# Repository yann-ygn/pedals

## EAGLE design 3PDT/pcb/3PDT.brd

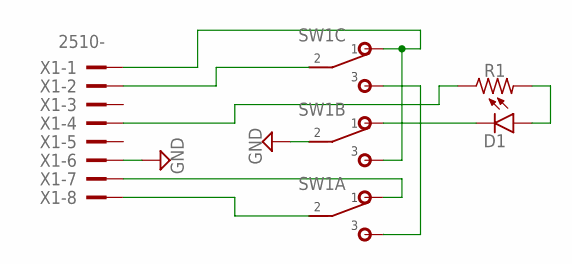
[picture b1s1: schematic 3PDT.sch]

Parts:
D1: LED; 3MM_D
R1: R_.3B; R0207/3
SW1: 3PDT
X1: 2510-; PAK100/2500-10

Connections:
GND: SW1.B2 (2), X1.6
unnamed: SW1.A3 (3), SW1.C3 (3)
unnamed: SW1.C2 (2), X1.2
unnamed: SW1.B3 (3), SW1.C1 (1), X1.1
unnamed: SW1.A2 (2), X1.8
unnamed: SW1.A1 (1), X1.7
unnamed: R1.1, X1.4
unnamed: D1.ANODE (A), R1.2
unnamed: D1.P$1 (C), SW1.B1 (1)

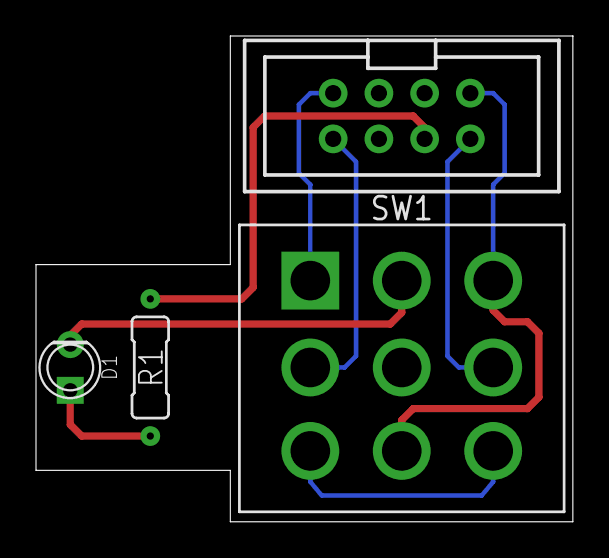
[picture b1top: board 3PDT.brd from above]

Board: 2 copper layers, 29.8 x 27.0 mm, 4 parts (0 on the bottom side), 9 nets.

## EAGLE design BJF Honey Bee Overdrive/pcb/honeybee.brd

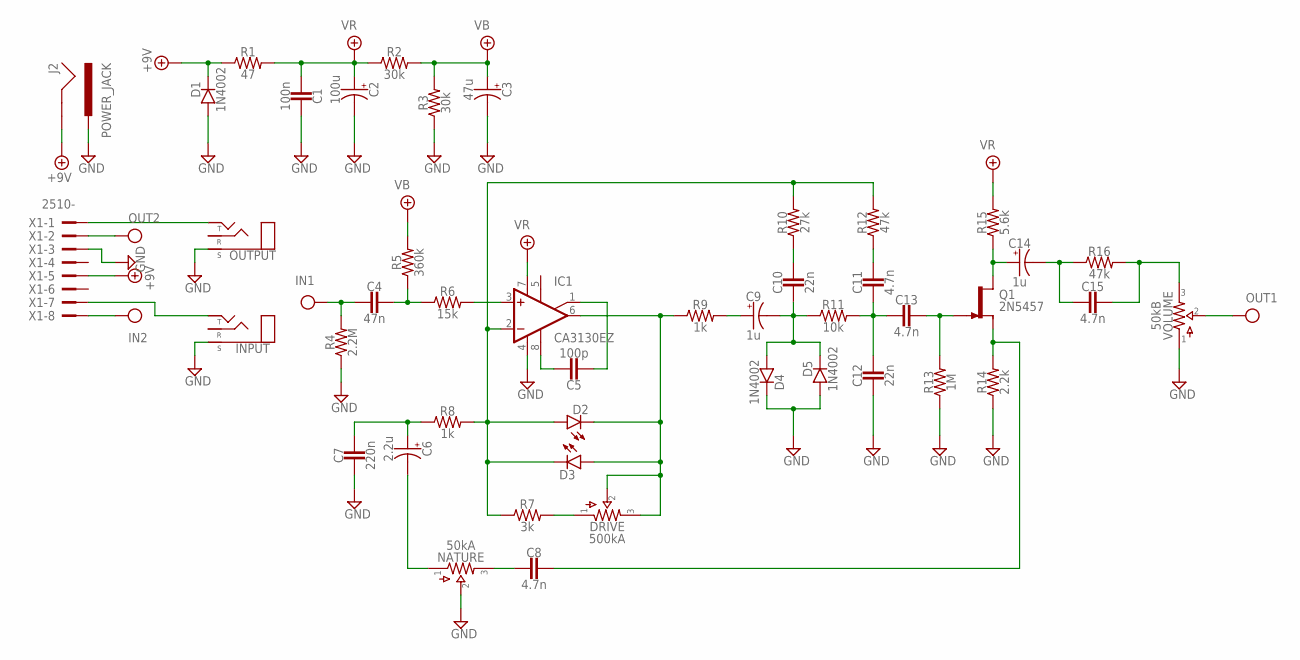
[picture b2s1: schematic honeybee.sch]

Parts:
C1: 100n; 050X030_025_2
C2: 100u; 040_020
C3: 47u; 040_020
C4: 47n; BOX_SMALL
C5: 100p; 050X030_025_2
C6: 2.2u; 050_020
C7: 220n; BOX_SMALL
C8, C11, C13, C15: 4.7n; BOX_SMALL
C9, C14: 1u; 040_020
C10, C12: 22n; BOX_SMALL
D1, D4, D5: 1N4002; DO41-2
D2, D3: LED; 3MM_D
DRIVE: 500kA; 16MM
IC1: CA3130EZ; DIL08
INPUT: STEREONMJ; NMJ6HCD2
J2: POWER_JACK; POWER_JACK_PTH
NATURE: 50kA; 16MM
OUTPUT: STEREONMJ; NMJ6HCD2
Q1: 2N5457; TO92-
R1: 47; R0207/3
R2, R3: 30k; R0207/3
R4: 2.2M; R0207/3
R5: 360k; R0207/3
R6: 15k; R0207/3
R7: 3k; R0207/3
R8, R9: 1k; R0207/3
R10: 27k; R0207/3
R11: 10k; R0207/3
R12, R16: 47k; R0207/3
R13: 1M; R0207/3
R14: 2.2k; R0207/3
R15: 5.6k; R0207/3
VOLUME: 50kB; 16MM
X1: 2510-; PAK100/2500-10

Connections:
+18V: D1.C, J2.GND, R1.1, X1.5
GND: C1.1, C2.-, C3.-, C7.2, C12.2, D1.A, D4.C, D5.A, IC1.4 (V-), INPUT.S, J2.PWR, NATURE.2, OUTPUT.S, R3.1, R4.1, R13.1, R14.1, VOLUME.1, X1.3
IN: C4.2, R4.2, X1.8
unnamed: C5.1, IC1.8 (CMP)
unnamed: C5.2, IC1.1 (ON/CMP)
unnamed: IC1.3 (+IN), R6.2
unnamed: C4.1, R5.1, R6.1
unnamed: D2.ANODE (A), D3.P$1 (C), IC1.2 (-IN), R7.1, R8.2, R10.2, R12.2
unnamed: DRIVE.1, R7.2
unnamed: D2.P$1 (C), D3.ANODE (A), DRIVE.2, DRIVE.3, IC1.6 (OUT), R9.1
unnamed: C6.+, C7.1, R8.1
unnamed: C6.-, NATURE.1
unnamed: C8.2, NATURE.3
unnamed: C9.-, C10.2, D4.A, D5.C, R11.1
unnamed: C13.1, Q1.1 (G), R13.2
unnamed: C9.+, R9.2
unnamed: C11.2, C12.1, C13.2, R11.2
unnamed: C11.1, R12.1
unnamed: C10.1, R10.1
unnamed: C8.1, Q1.2 (S), R14.2
unnamed: C14.+, Q1.3 (D), R15.1
unnamed: C14.-, C15.2, R16.1
unnamed: C15.1, R16.2, VOLUME.3
unnamed: OUTPUT.T, X1.1
unnamed: INPUT.T, X1.7
OUT: VOLUME.2, X1.2
VB: C3.+, R2.2, R3.2, R5.2
VR: C1.2, C2.+, IC1.7 (V+), R1.2, R2.1, R15.2

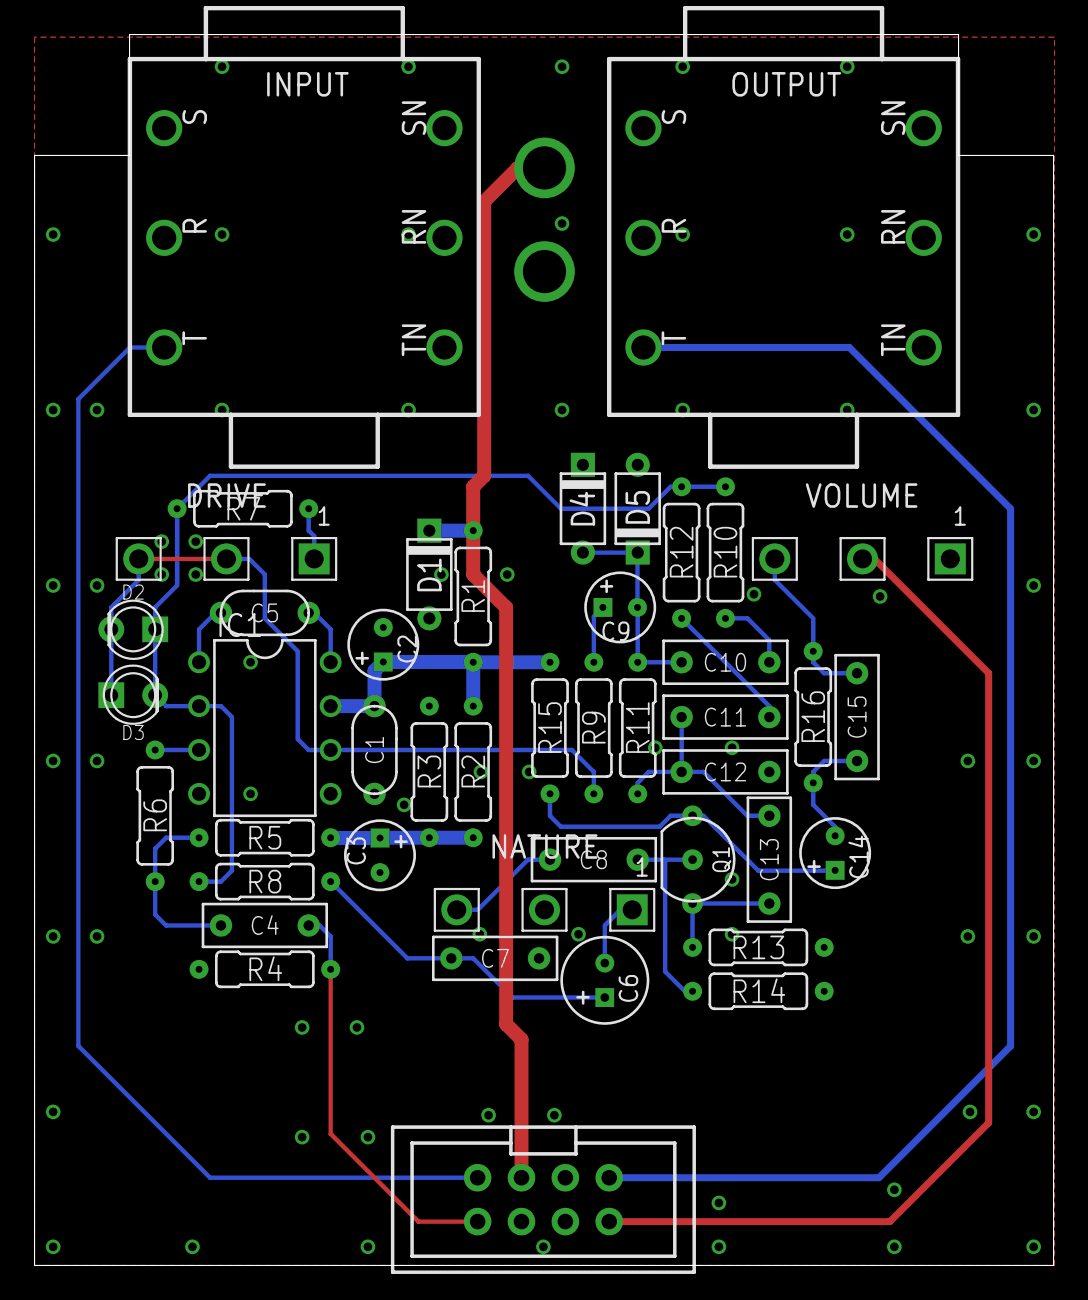
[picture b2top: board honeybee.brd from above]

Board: 2 copper layers, 59.0 x 71.3 mm, 46 parts (1 on the bottom side), 28 nets.

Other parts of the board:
U$1: 125B_PCB

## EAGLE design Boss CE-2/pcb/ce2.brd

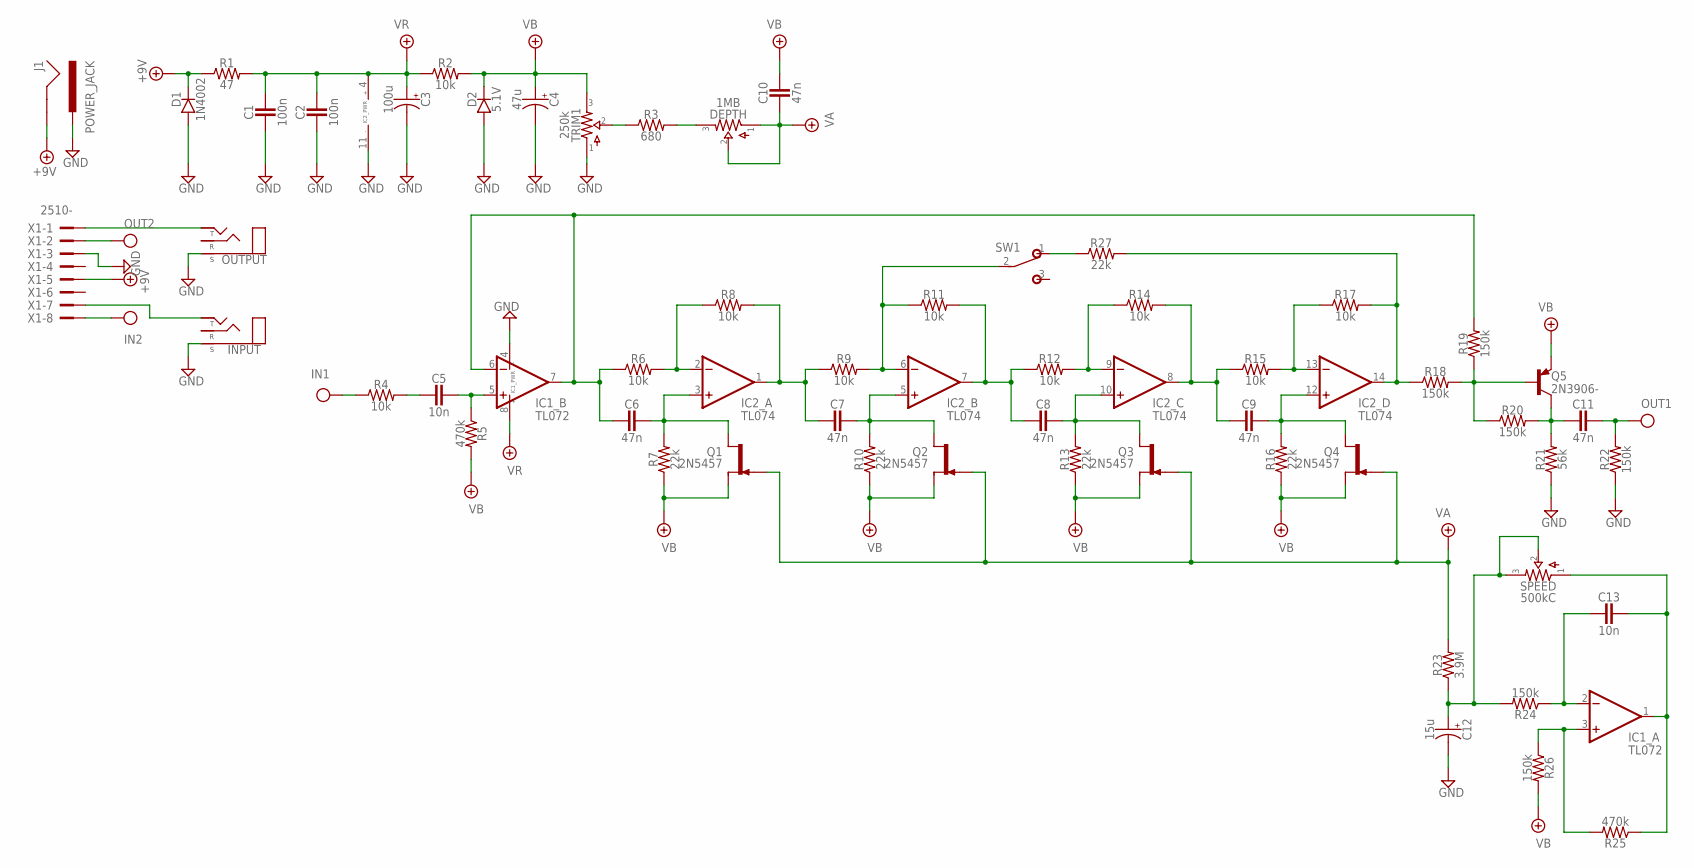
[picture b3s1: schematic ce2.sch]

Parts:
C1, C2: 100n; 050X030_025_2
C3: 100u; 050_020
C4: 47u; 050_020
C5, C13: 10n; BOX_SMALL
C6, C7, C8, C9, C10, C11: 47n; BOX_SMALL
C12: 15u; 050_020_1
D1: 1N4002; DO41-2
D2: 5.1V; DO41-2
DEPTH: 1MB; 16MM
IC1: TL072; DIL0
IC2: TL074; DIL14
INPUT: STEREONMJ; NMJ6HCD2
J1: POWER_JACK; POWER_JACK_PTH
OUTPUT: STEREONMJ; NMJ6HCD2
Q1, Q2, Q3, Q4: 2N5457; TO92-
Q5: 2N3906-; TO92-
R1: 47; R0207/3
R2, R4, R6, R8, R9, R11, R12, R14, R15, R17: 10k; R0207/3
R3: 680; R0207/3
R5, R25: 470k; R0207/3
R7, R10, R13, R16, R27: 22k; R0207/3
R18, R19, R20, R22, R24, R26: 150k; R0207/3
R21: 56k; R0207/3
R23: 3.9M; R0207/3
SPEED: 500kC; 16MM
SW1: SPDTPIN_MOUNT; 1MS1T1B1C0M2QE
TRIM1: 250k; RTRIM3296W
X1: 2510-; PAK100/2500-10

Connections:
+9V: D1.C, J1.GND, R1.1, X1.5
GND: C1.2, C2.2, C3.-, C4.-, C12.-, D1.A, D2.A, IC1.4 (V-), IC2.11 (V-), INPUT.S, J1.PWR, OUTPUT.S, R21.1, R22.1, TRIM1.1, X1.3
IN: R4.1, X1.8
unnamed: R3.1, TRIM1.2
unnamed: INPUT.T, X1.7
unnamed: DEPTH.3, R3.2
unnamed: OUTPUT.T, X1.1
unnamed: C5.2, R4.2
unnamed: C6.2, IC1.6 (-IN), IC1.7 (OUT), R6.1, R19.2
unnamed: IC2.2 (-IN), R6.2, R8.1
unnamed: C5.1, IC1.5 (+IN), R5.1
unnamed: C6.1, IC2.3 (+IN), Q1.3 (D), R7.2
unnamed: C7.2, IC2.1 (OUT), R8.2, R9.1
unnamed: R27.1, SW1.1 (O)
unnamed: IC2.6 (-IN), R9.2, R11.1, SW1.2
unnamed: C7.1, IC2.5 (+IN), Q2.3 (D), R10.2
unnamed: C8.2, IC2.7 (OUT), R11.2, R12.1
unnamed: IC1.3 (+IN), R25.2, R26.1
unnamed: IC2.9 (-IN), R12.2, R14.1
unnamed: C8.1, IC2.10 (+IN), Q3.3 (D), R13.2
unnamed: C9.2, IC2.8 (OUT), R14.2, R15.1
unnamed: C13.1, IC1.1 (OUT), R25.1, SPEED.1
unnamed: IC2.13 (-IN), R15.2, R17.1
unnamed: C9.1, IC2.12 (+IN), Q4.3 (D), R16.2
unnamed: IC2.14 (OUT), R17.2, R18.1, R27.2
unnamed: Q5.2 (B), R18.2, R19.1, R20.1
unnamed: C11.2, Q5.1 (C), R20.2, R21.2
unnamed: C13.2, IC1.2 (-IN), R24.1
unnamed: C12.+, R23.1, R24.2, SPEED.2, SPEED.3
OUT: C11.1, R22.2, X1.2
VA: C10.2, DEPTH.1, DEPTH.2, Q1.1 (G), Q2.1 (G), Q3.1 (G), Q4.1 (G), R23.2
VB: C4.+, C10.1, D2.C, Q1.2 (S), Q2.2 (S), Q3.2 (S), Q4.2 (S), Q5.3 (E), R2.2, R5.2, R7.1, R10.1, R13.1, R16.1, R26.2, TRIM1.3
VR: C1.1, C2.1, C3.+, IC1.8 (V+), IC2.4 (V+), R1.2, R2.1

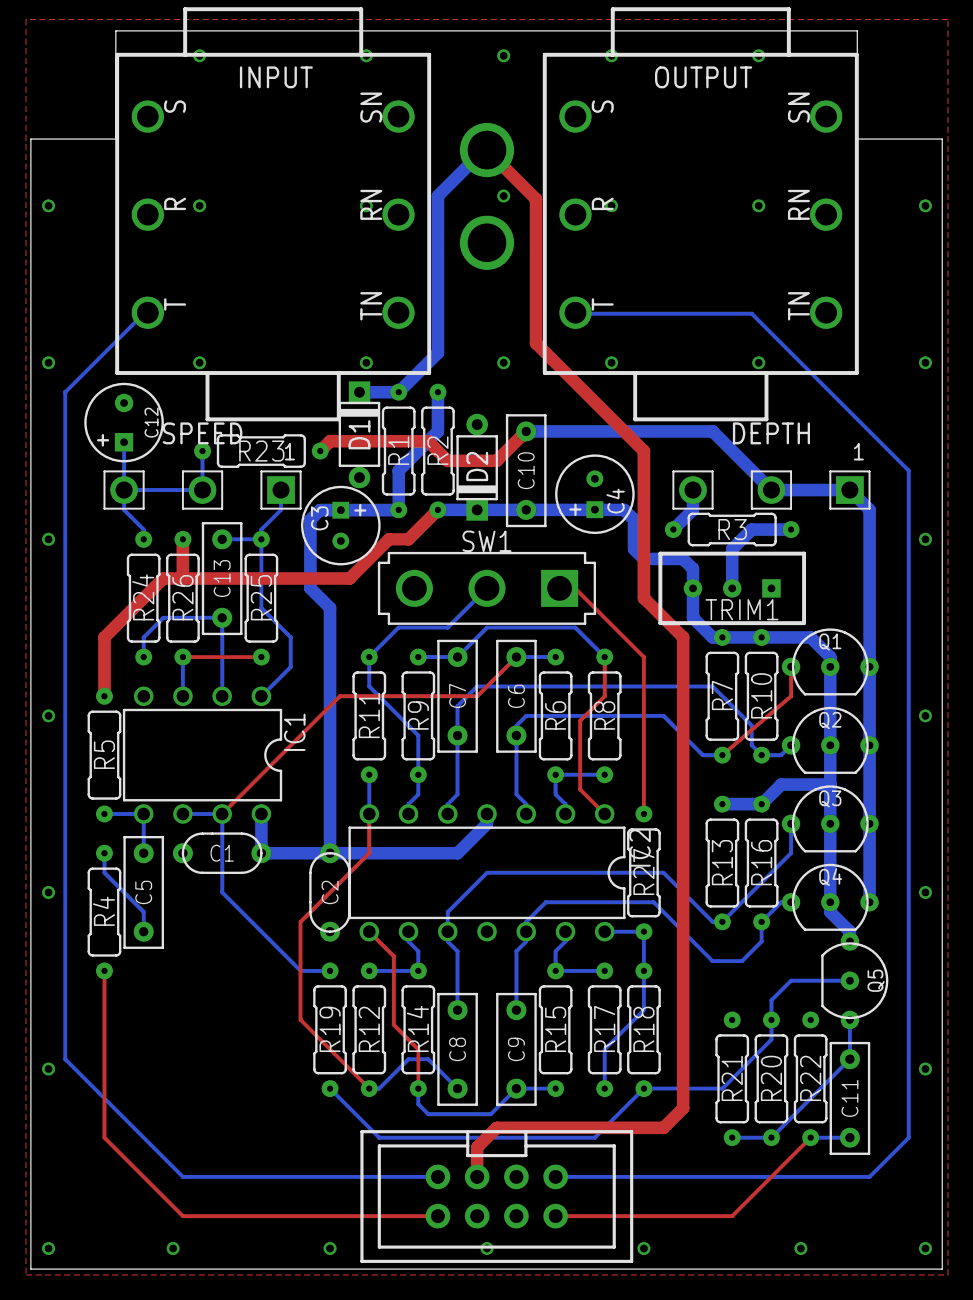
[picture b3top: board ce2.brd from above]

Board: 2 copper layers, 59.0 x 80.2 mm, 58 parts (1 on the bottom side), 33 nets.

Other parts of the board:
U$2: 125B_PCB_HUGE

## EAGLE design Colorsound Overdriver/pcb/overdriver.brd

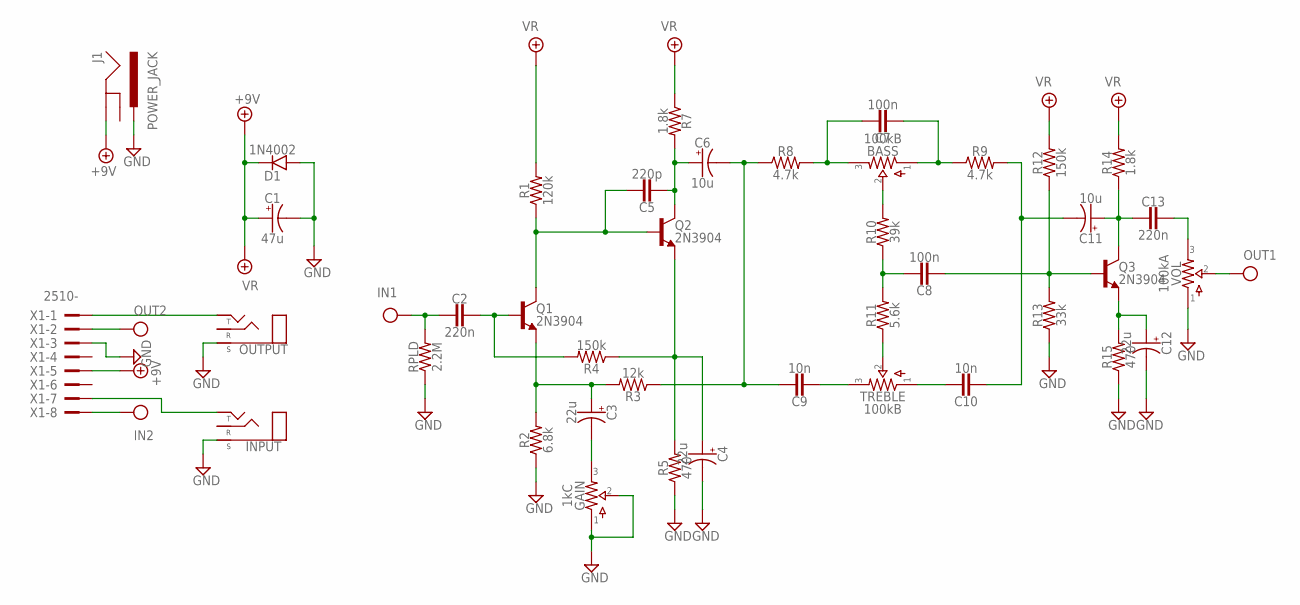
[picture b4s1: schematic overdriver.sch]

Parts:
BASS: 100kB; 16MM
C1: 47u; 040_020
C2, C13: 220n; BOX_SMALL
C3, C4, C12: 22u; 040_020
C5: 220p; 050X030_025_2
C6, C11: 10u; 050_020_1
C7, C8: 100n; BOX_SMALL
C9, C10: 10n; BOX_SMALL
D1: 1N4002; DO41-2
GAIN: 1kC; 16MM
INPUT: STEREONMJ; NMJ6HCD2
J1: POWER_JACK; POWER_JACK_PTH
OUTPUT: STEREONMJ; NMJ6HCD2
Q1, Q2, Q3: 2N3904; TO92-
R1: 120k; R0207/3
R2: 6.8k; R0207/3
R3: 12k; R0207/3
R4, R12: 150k; R0207/3
R5, R15: 470; R0207/3
R7, R14: 1.8k; R0207/3
R8, R9: 4.7k; R0207/3
R10: 39k; R0207/3
R11: 5.6k; R0207/3
R13: 33k; R0207/3
RPLD: 2.2M; R0207/3
TREBLE: 100kB; 16MM
VOL: 100kA; 16MM
X1: 2510-; PAK100/2500-10

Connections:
+9V: C1.+, D1.C, J1.GND, X1.5
GND: C1.-, C4.-, C12.-, D1.A, GAIN.1, GAIN.2, INPUT.S, J1.PWR, OUTPUT.S, R2.1, R5.1, R13.1, R15.1, RPLD.1, VOL.1, X1.3
IN: C2.2, RPLD.2, X1.8
unnamed: INPUT.T, X1.7
unnamed: OUTPUT.T, X1.1
unnamed: C5.1, Q1.1 (C), Q2.2 (B), R1.1
unnamed: C2.1, Q1.2 (B), R4.2
unnamed: C3.+, Q1.3 (E), R2.2, R3.2
unnamed: C3.-, GAIN.3
unnamed: C5.2, C6.+, Q2.1 (C), R7.2
unnamed: C6.-, C9.1, R3.1, R8.1
unnamed: C4.+, Q2.3 (E), R4.1, R5.2
unnamed: BASS.3, C7.1, R8.2
unnamed: BASS.1, C7.2, R9.1
unnamed: BASS.2, R10.2
unnamed: R11.1, TREBLE.2
unnamed: C8.1, R10.1, R11.2
unnamed: C9.2, TREBLE.3
unnamed: C10.1, TREBLE.1
unnamed: C10.2, C11.-, R9.2
unnamed: C8.2, Q3.2 (B), R12.1, R13.2
unnamed: C11.+, C13.2, Q3.1 (C), R14.1
unnamed: C12.+, Q3.3 (E), R15.2
unnamed: C13.1, VOL.3
OUT: VOL.2, X1.2
VR: R1.2, R7.1, R12.2, R14.2

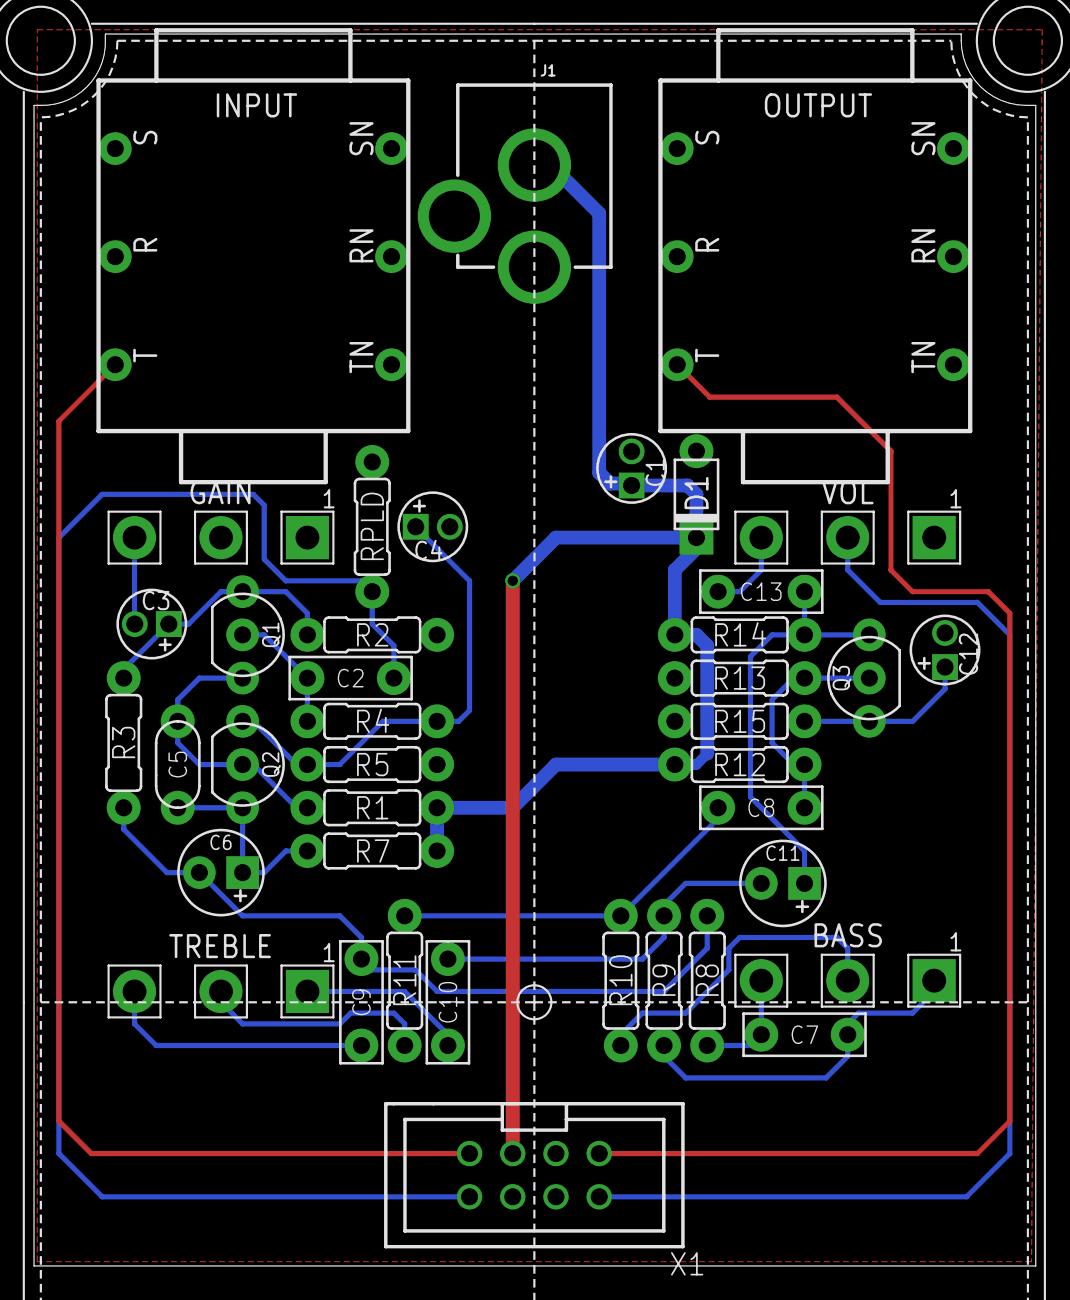
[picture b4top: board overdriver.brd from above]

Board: 2 copper layers, 58.9 x 72.4 mm, 41 parts (0 on the bottom side), 26 nets.

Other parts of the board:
U$1: 125B

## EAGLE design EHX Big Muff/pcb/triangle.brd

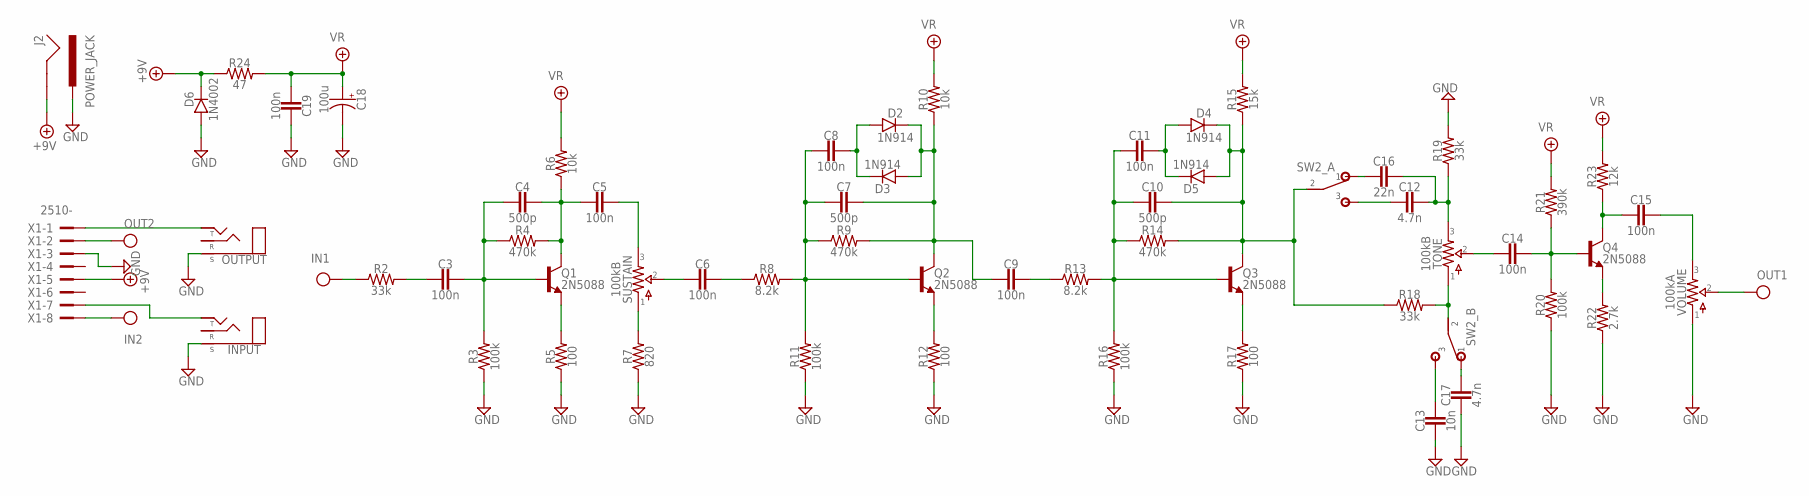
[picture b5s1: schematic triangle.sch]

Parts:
C3, C5, C6, C8, C9, C11, C14, C15: 100n; BOX_SMALL
C4, C7, C10: 500p; 050X030_025_2
C12, C17: 4.7n; BOX_SMALL
C13: 10n; BOX_SMALL
C16: 22n; BOX_SMALL
C18: 100u; 050_020
C19: 100n; 050X030_025_2
D2, D3, D4, D5: 1N914; DO35-2
D6: 1N4002; DO41-2
INPUT: STEREONMJ; NMJ6HCD2
J2: POWER_JACK; POWER_JACK_PTH
OUTPUT: STEREONMJ; NMJ6HCD2
Q1, Q2, Q3, Q4: 2N5088; TO92-
R2, R18, R19: 33k; R0207/3
R3, R11, R16, R20: 100k; R0207/3
R4, R9, R14: 470k; R0207/3
R5, R12, R17: 100; R0207/3
R6, R10: 10k; R0207/3
R7: 820; R0207/3
R8, R13: 8.2k; R0207/3
R15: 15k; R0207/3
R21: 390k; R0207/3
R22: 2.7k; R0207/3
R23: 12k; R0207/3
R24: 47; R0207/3
SUSTAIN: 100kB; 16MM
SW2: DPDT
TONE: 100kB; 16MM
VOLUME: 100kA; 16MM
X1: 2510-; PAK100/2500-10

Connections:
+18V: D6.C, J2.GND, R24.1, X1.5
GND: C13.2, C17.2, C18.-, C19.1, D6.A, INPUT.S, J2.PWR, OUTPUT.S, R3.1, R5.1, R7.1, R11.1, R12.1, R16.1, R17.1, R19.2, R20.1, R22.1, VOLUME.1, X1.3
IN: R2.1, X1.8
unnamed: C3.2, R2.2
unnamed: C3.1, C4.2, Q1.2 (B), R3.2, R4.1
unnamed: Q1.3 (E), R5.2
unnamed: C4.1, C5.2, Q1.1 (C), R4.2, R6.1
unnamed: R7.2, SUSTAIN.1
unnamed: C5.1, SUSTAIN.3
unnamed: C6.2, SUSTAIN.2
unnamed: C6.1, R8.1
unnamed: C7.2, C8.2, Q2.2 (B), R8.2, R9.1, R11.2
unnamed: Q2.3 (E), R12.2
unnamed: C9.1, R13.1
unnamed: C8.1, D2.A, D3.C
unnamed: C7.1, C9.2, D2.C, D3.A, Q2.1 (C), R9.2, R10.1
unnamed: C10.2, C11.2, Q3.2 (B), R13.2, R14.1, R16.2
unnamed: Q3.3 (E), R17.2
unnamed: C11.1, D4.A, D5.C
unnamed: C10.1, D4.C, D5.A, Q3.1 (C), R14.2, R15.1, R18.1, SW2.A2 (2)
unnamed: R18.2, SW2.B2 (2), TONE.1
unnamed: C17.1, SW2.B1 (1)
unnamed: C14.2, TONE.2
unnamed: C14.1, Q4.2 (B), R20.2, R21.1
unnamed: Q4.3 (E), R22.2
unnamed: C15.2, Q4.1 (C), R23.1
unnamed: C15.1, VOLUME.3
unnamed: C12.2, SW2.A3 (3)
unnamed: C16.2, SW2.A1 (1)
unnamed: C12.1, C16.1, R19.1, TONE.3
unnamed: C13.1, SW2.B3 (3)
unnamed: OUTPUT.T, X1.1
unnamed: INPUT.T, X1.7
OUT: VOLUME.2, X1.2
VR: C18.+, C19.2, R6.2, R10.2, R15.2, R21.2, R23.2, R24.2

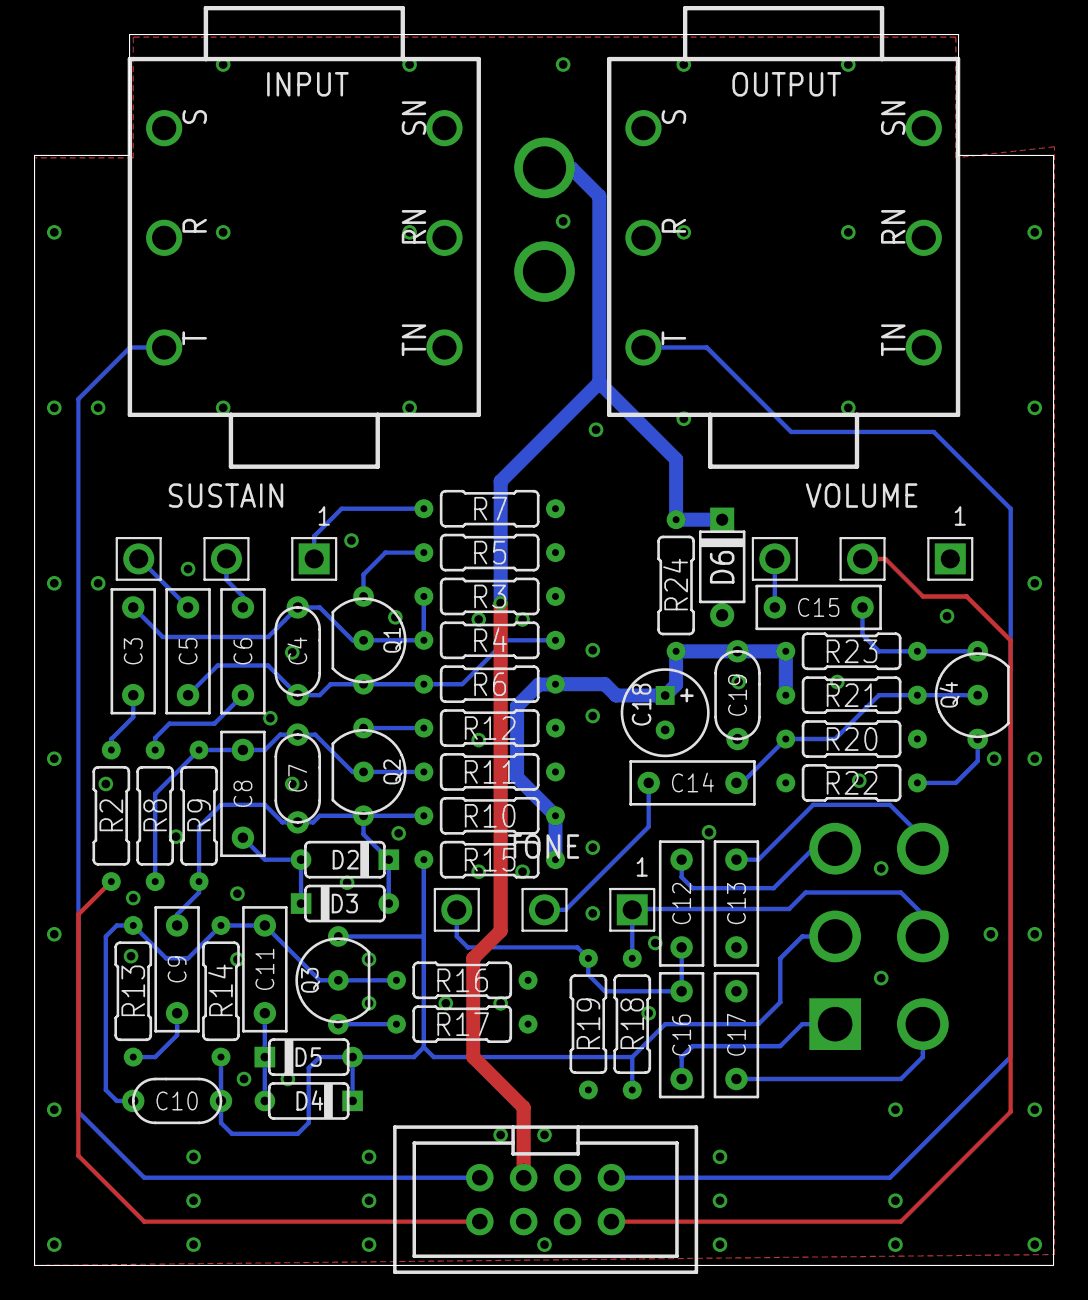
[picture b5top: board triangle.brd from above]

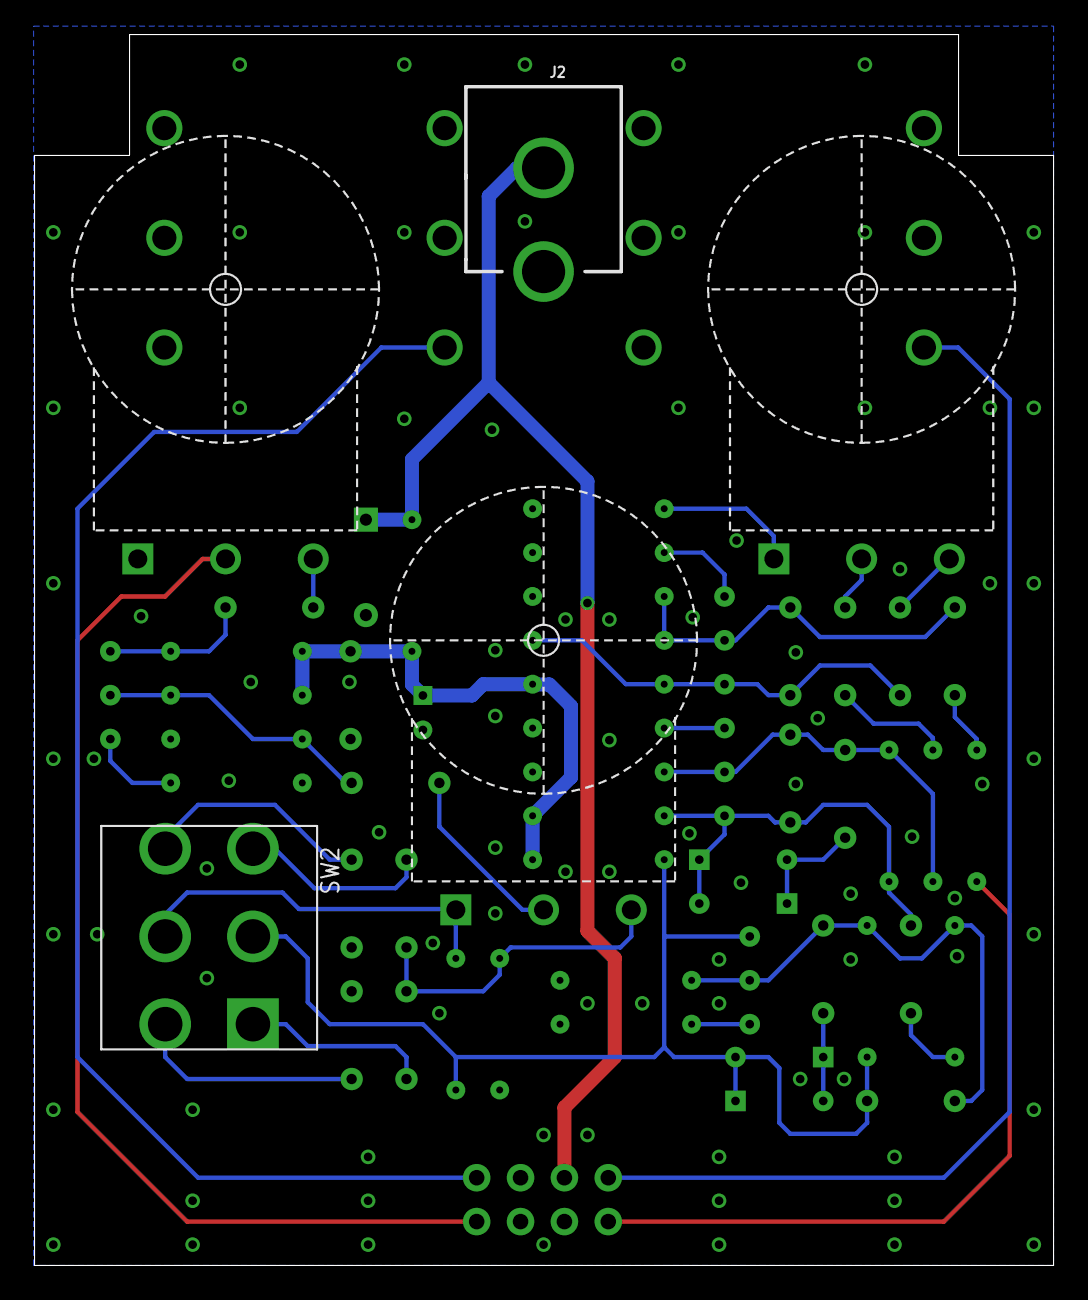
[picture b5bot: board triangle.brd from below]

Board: 2 copper layers, 59.0 x 71.3 mm, 58 parts (2 on the bottom side), 35 nets.

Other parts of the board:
U$1: 125B_PCB

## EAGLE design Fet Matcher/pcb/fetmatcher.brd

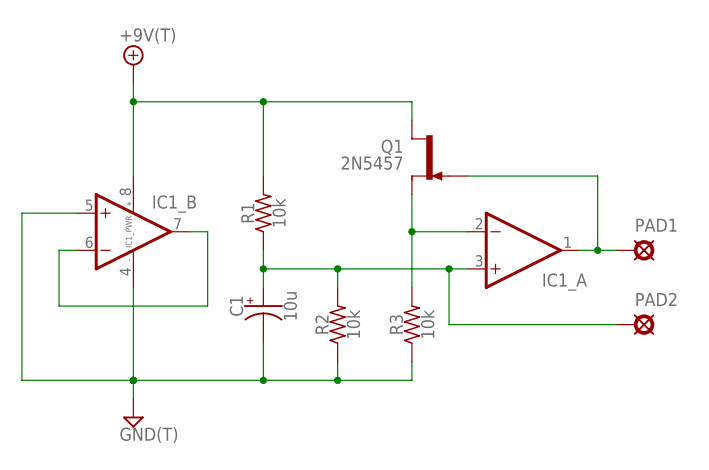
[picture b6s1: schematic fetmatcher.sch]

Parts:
+9V1: +9V(T); SQUARE
C1: 10u; 050_020_1
GND1: GND(T); SQUARE
IC1: DUALTH; DIL0
PAD1, PAD2: PAD; SQUARE
Q1: 2N5457; TO92-
R1, R2, R3: 10k; R0207/3

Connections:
+9V: +9V1.1, IC1.8 (V+), Q1.3 (D), R1.2
GND: C1.-, GND1.1, IC1.4 (V-), IC1.5 (+IN), R2.1, R3.1
unnamed: IC1.6 (-IN), IC1.7 (OUT)
unnamed: IC1.2 (-IN), Q1.2 (S), R3.2
unnamed: C1.+, IC1.3 (+IN), PAD2.1, R1.1, R2.2
unnamed: IC1.1 (OUT), PAD1.1, Q1.1 (G)

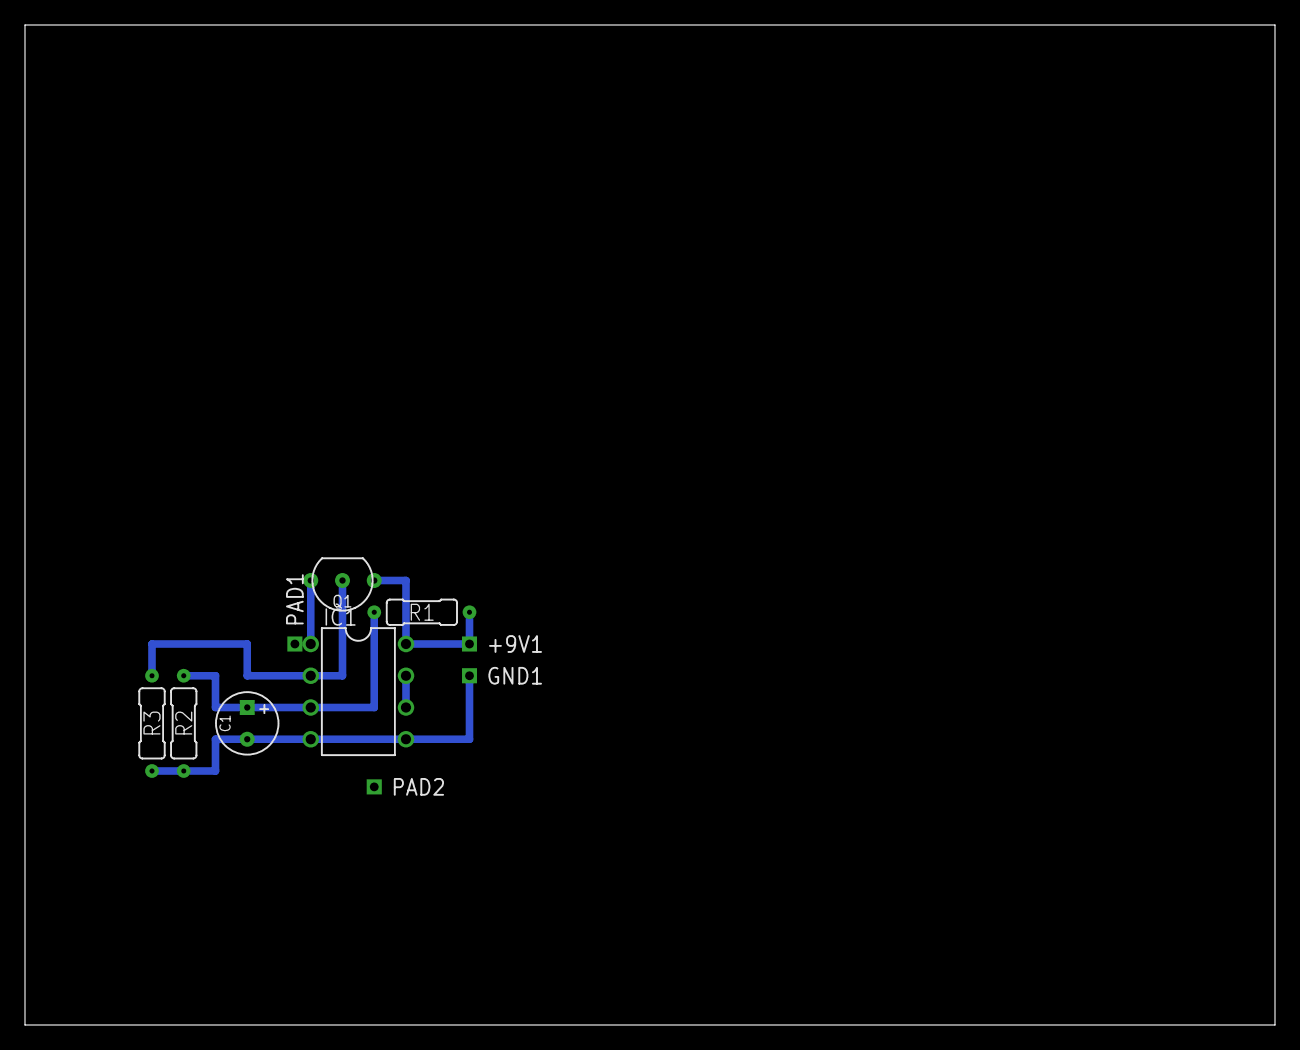
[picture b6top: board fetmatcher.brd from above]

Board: 2 copper layers, 100.0 x 80.0 mm, 10 parts (0 on the bottom side), 6 nets.
